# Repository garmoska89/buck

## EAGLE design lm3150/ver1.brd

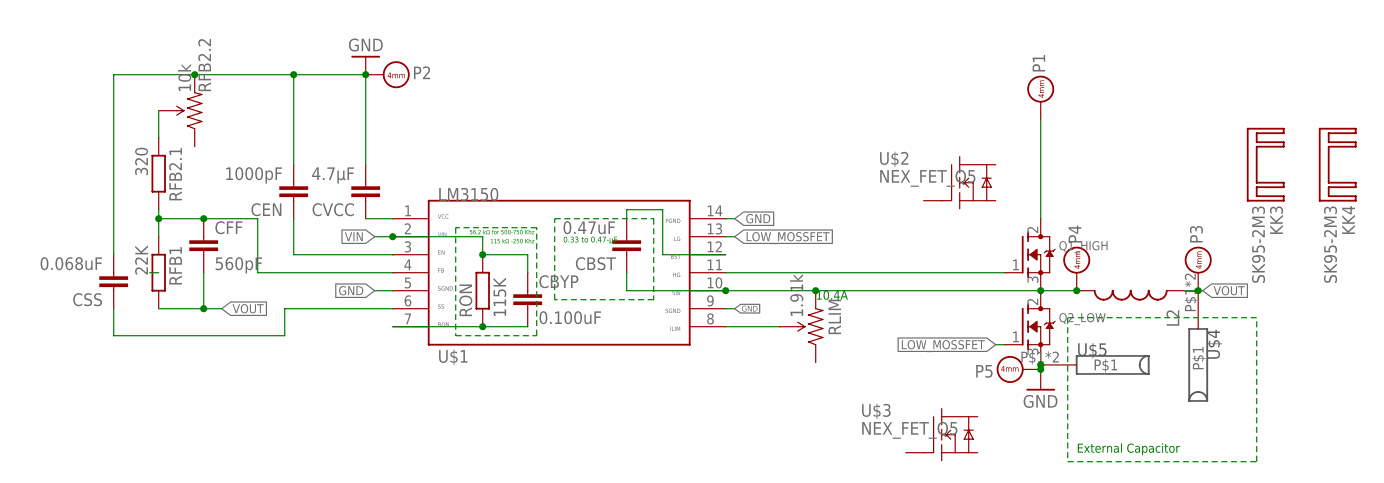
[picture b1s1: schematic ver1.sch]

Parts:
CBST: 0.47uF; 0805
CBYP: 0.100uF; 0805
CEN: 1000pF; 0805
CFF: 560pF; 0805
CSS: 0.068uF; 0805
CVCC: 4.7µF; 0805
KK3, KK4: SK95-2M3
L2: INDUCTOR; INDUCTOR-SRP4020
P1, P2, P3, P4, P5: BANANA
Q1_HIGH, Q2_LOW: MOSFET-NGDS_TO220V; TO220V
RFB1: 22K; R805
RFB2.1: 320; R805
RFB2.2: 10k; 3362U-2
RLIM: 1.91k; 3362U-2
RON: 115K; R805
U$1: LM3150; HTSSOP14
U$2, U$3: NEX_FET_Q5; Q5
U$4, U$5: BANANA

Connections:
GND: CEN.2, CSS.2, CVCC.2, P2.P$1, P5.P$1, Q2_LOW.3 (S), RFB2.2.3 (CW), U$1.5, U$1.9, U$1.14, U$5.P$1, U$5.P$2
HIGH_MOSSFET: Q1_HIGH.1 (G), U$1.11
LOW_MOSSFET: Q2_LOW.1 (G), U$1.13
unnamed: CVCC.1, U$1.1
unnamed: CBYP.2, RON.1, U$1.7
unnamed: CEN.1, U$1.3
unnamed: CSS.1, U$1.6
unnamed: CFF.1, RFB1.1, RFB2.1.2, U$1.4
unnamed: RFB2.1.1, RFB2.2.2 (WIPER)
unnamed: CBST.2, U$1.12
unnamed: RLIM.2 (WIPER), U$1.8
unnamed: CBST.1, L2.P$2 (2), P4.P$1, Q1_HIGH.3 (S), Q2_LOW.2 (D), RLIM.3 (CW), U$1.10
VIN: CBYP.1, P1.P$1, Q1_HIGH.2 (D), RON.2, U$1.2
VOUT: CFF.2, L2.P$1 (1), P3.P$1, RFB1.2

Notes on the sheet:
115 kΩ -250 Khz
56,2 kΩ for 500-750 Khz
0.33 to 0.47-µF
10.4A
External Capacitor

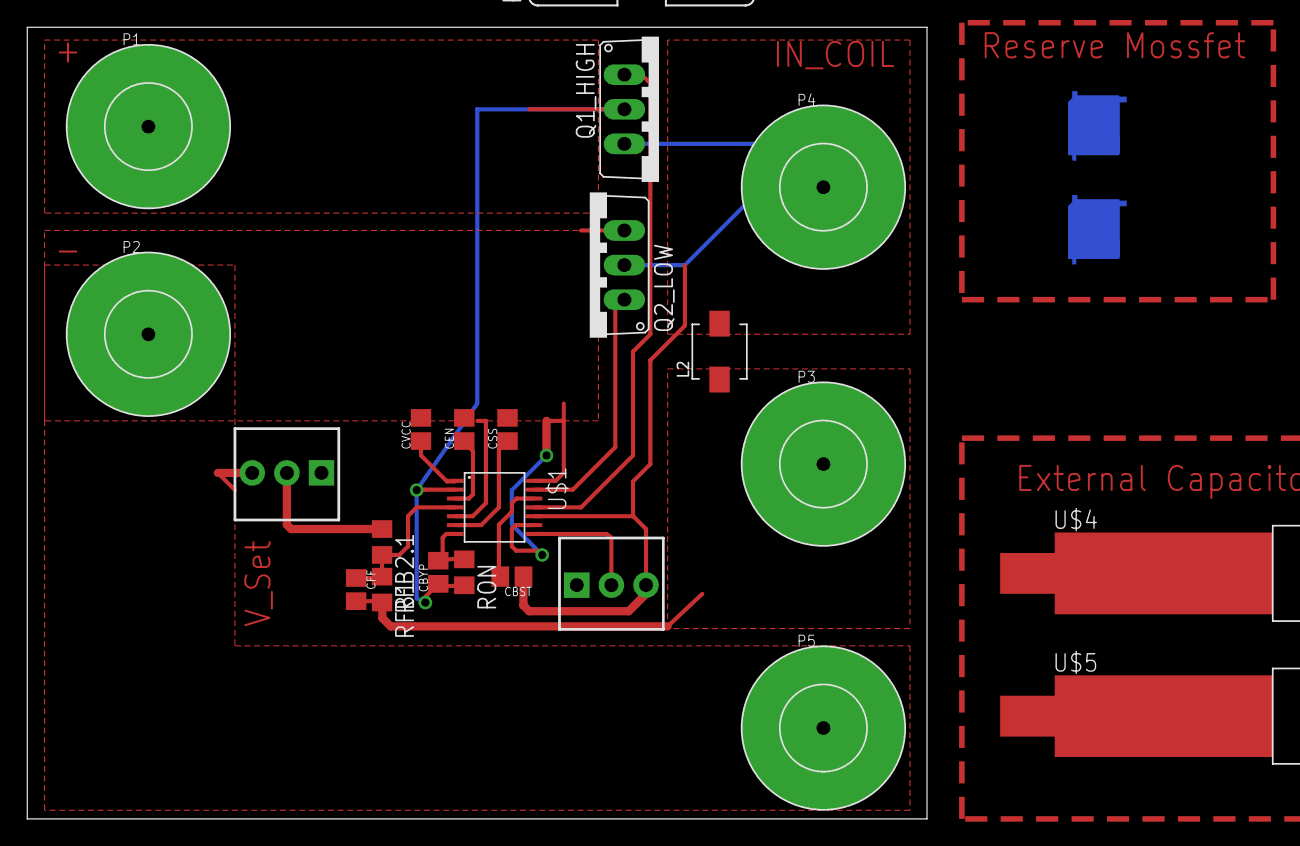
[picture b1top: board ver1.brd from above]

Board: 2 copper layers, 66.0 x 58.1 mm, 26 parts (0 on the bottom side), 14 nets.

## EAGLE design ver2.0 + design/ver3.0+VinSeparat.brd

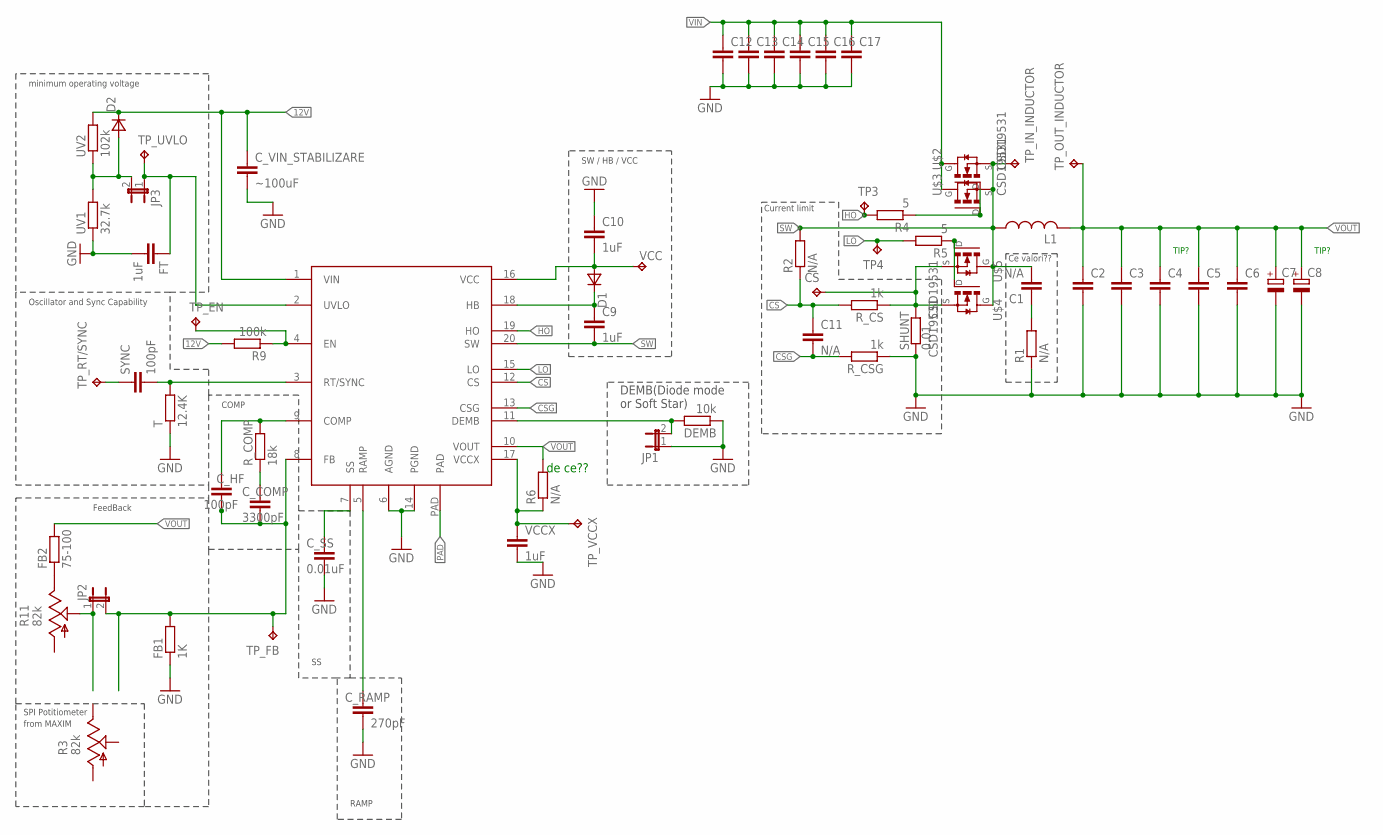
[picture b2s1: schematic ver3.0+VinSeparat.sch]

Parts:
C1, C11: N/A; C0805K
C2, C3, C4, C5, C6: C-EUC1812; C1812
C7, C8: CPOL-EU153CLV-1012; 153CLV-1012
C9, C10: 1uF; C0805K
C12, C13, C14, C15, C16, C17: C-EUC1812K; C1812K
CS: TPPAD1-20; P1-20
C_COMP: 3300pF; C0805K
C_HF: 100pF; C0805K
C_RAMP: 270pF; C0805K
C_SS: 0.01uF; C0805K
C_VIN_STABILIZARE: ~100uF; C0805K
D1, D2: DSOT23; SOT-23
DEMB: 10k; R0603
FB1: 1K; R0603
FB2: 75-100; R0603
FT: 1uF; C1812K
JP1, JP2, JP3: JP1E; JP1
L1: L-USTJ8-U2; TJ8-U2
R1: N/A; M1206
R2, R6: N/A; R0603
R3, R11: 82k; B64Y
R4, R5: 5; M1206
R9: 100k; R0603
R_COMP: 18k; R0603
R_CS: 1k; R0603
R_CSG: 1k; R0603
SHUNT: 0.01; SMR-0
SYNC: 100pF; C0805K
T: 12.4K; R0603
TP3, TP4: TPPAD1-20; P1-20
TP_EN: TPPAD1-20; P1-20
TP_FB: TPPAD1-20; P1-20
TP_IN_INDUCTOR: TPPAD1-20; P1-20
TP_OUT_INDUCTOR: TPPAD1-20; P1-20
TP_RT/SYNC: TPPAD1-20; P1-20
TP_UVLO: TPPAD1-20; P1-20
TP_VCCX: TPPAD1-20; P1-20
U$1: LM5116; TSSOP20
U$2, U$3, U$4, U$5: CSD19531; TO220H
UV1: 32.7k; R0603
UV2: 102k; R0603
VCC: TPPAD1-20; P1-20
VCCX: 1uF; C0805K

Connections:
12V: C_VIN_STABILIZARE.1, D2.1 (C), R9.2, U$1.1 (VIN), UV2.2
CS: C11.1, R2.1, R_CS.2, U$1.12 (CS)
CSG: C11.2, R_CSG.2, U$1.13 (CSG)
DEMB: DEMB.2, JP1.2, U$1.11 (DEMB)
GND: C2.2, C3.2, C4.2, C5.2, C6.2, C7.-, C8.-, C10.1, C12.2, C13.2, C14.2, C15.2, C16.2, C17.2, C_RAMP.2, C_SS.2, C_VIN_STABILIZARE.2, DEMB.1, FB1.1, FT.2, JP1.1, R1.1, R_CSG.1, SHUNT.2, T.1, U$1.6 (AGND), U$1.14 (PGND), UV1.1, VCCX.2
HB: C9.1, D1.1 (C), U$1.18 (HB)
HO: R4.2, TP3.TP, U$1.19 (HO)
LO: R5.2, TP4.TP, U$1.15 (LO)
unnamed: R6.1, TP_VCCX.TP, U$1.17 (VCCX), VCCX.1
unnamed: C1.1, R1.2
unnamed: CS.TP, R_CS.1, SHUNT.1, U$4.3 (S), U$5.3 (S)
unnamed: R9.1, TP_EN.TP, U$1.4 (EN)
unnamed: SYNC.2, T.2, U$1.3 (RT/SYNC)
unnamed: R4.1, U$2.1 (G), U$3.1 (G)
unnamed: SYNC.1, TP_RT/SYNC.TP
unnamed: FB2.1, R11.E
unnamed: C_HF.1, R_COMP.2, U$1.9 (COMP)
unnamed: C_COMP.1, R_COMP.1
unnamed: C_SS.1, U$1.7 (SS)
unnamed: C_RAMP.1, U$1.5 (RAMP)
unnamed: JP2.1, R11.S
unnamed: FT.1, JP3.1, TP_UVLO.TP, U$1.2 (UVLO)
unnamed: C_COMP.2, C_HF.2, FB1.2, JP2.2, TP_FB.TP, U$1.8 (FB)
unnamed: R5.1, U$4.1 (G), U$5.1 (G)
PAD: U$1.PAD
SW: C1.2, C9.2, L1.1, R2.2, TP_IN_INDUCTOR.TP, U$1.20 (SW), U$2.3 (S), U$3.3 (S), U$4.2 (D), U$4.T (D), U$5.2 (D), U$5.T (D)
UVLO: D2.3 (A), JP3.2, UV1.2, UV2.1
VCC: C10.2, D1.3 (A), U$1.16 (VCC), VCC.TP
VIN: C12.1, C13.1, C14.1, C15.1, C16.1, C17.1, U$2.2 (D), U$2.T (D), U$3.2 (D), U$3.T (D)
VOUT: C2.1, C3.1, C4.1, C5.1, C6.1, C7.+, C8.+, FB2.2, L1.2, R6.2, TP_OUT_INDUCTOR.TP, U$1.10 (VOUT)

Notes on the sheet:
TIP?
minimum operating voltage
Oscillator and Sync Capability
COMP
FeedBack
RAMP
DEMB(Diode mode or Soft Star)
SW / HB / VCC
Current limit
SPI Potitiometer
from MAXIM
Ce valori??
de ce??

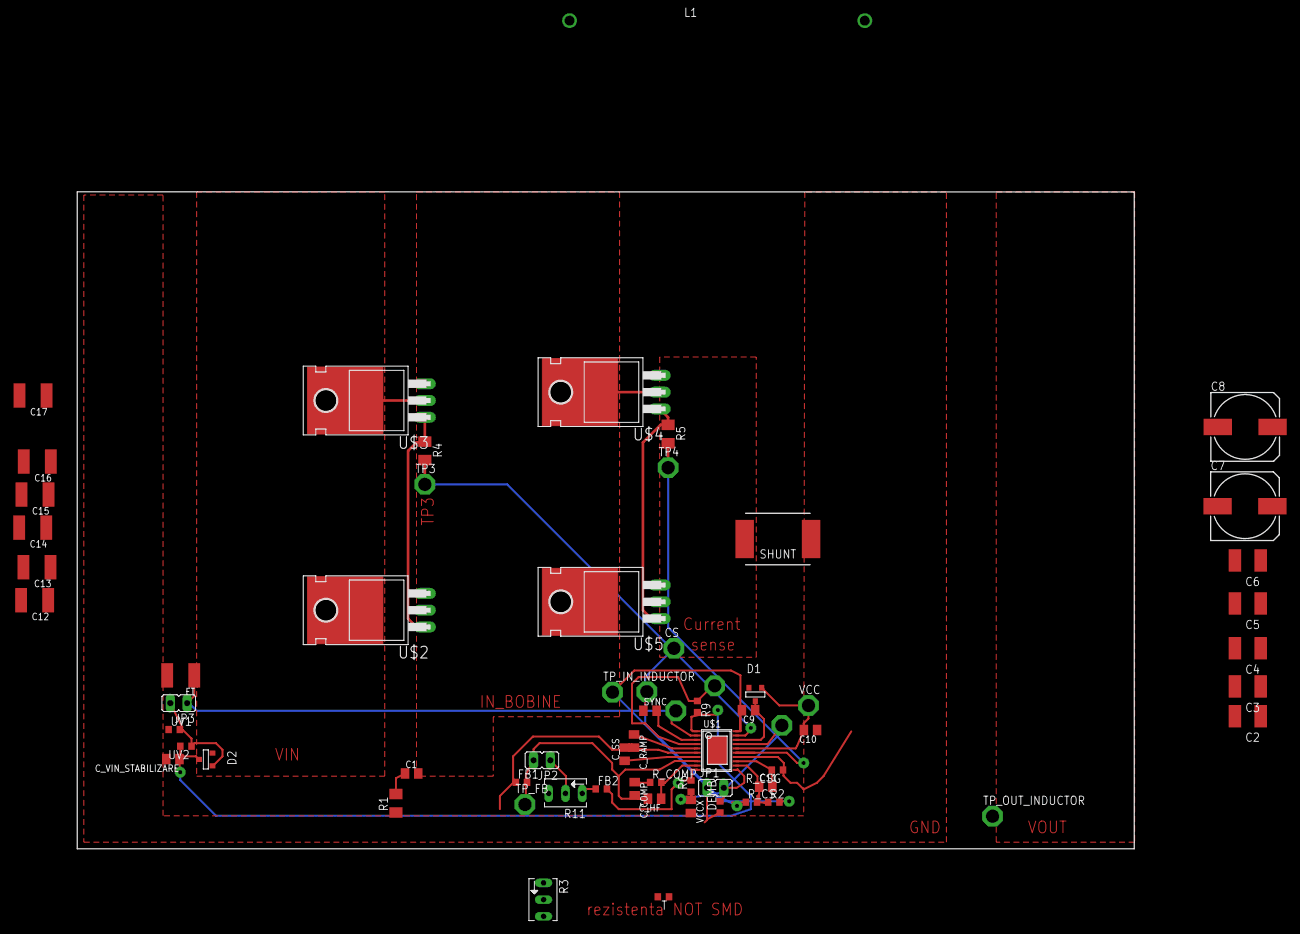
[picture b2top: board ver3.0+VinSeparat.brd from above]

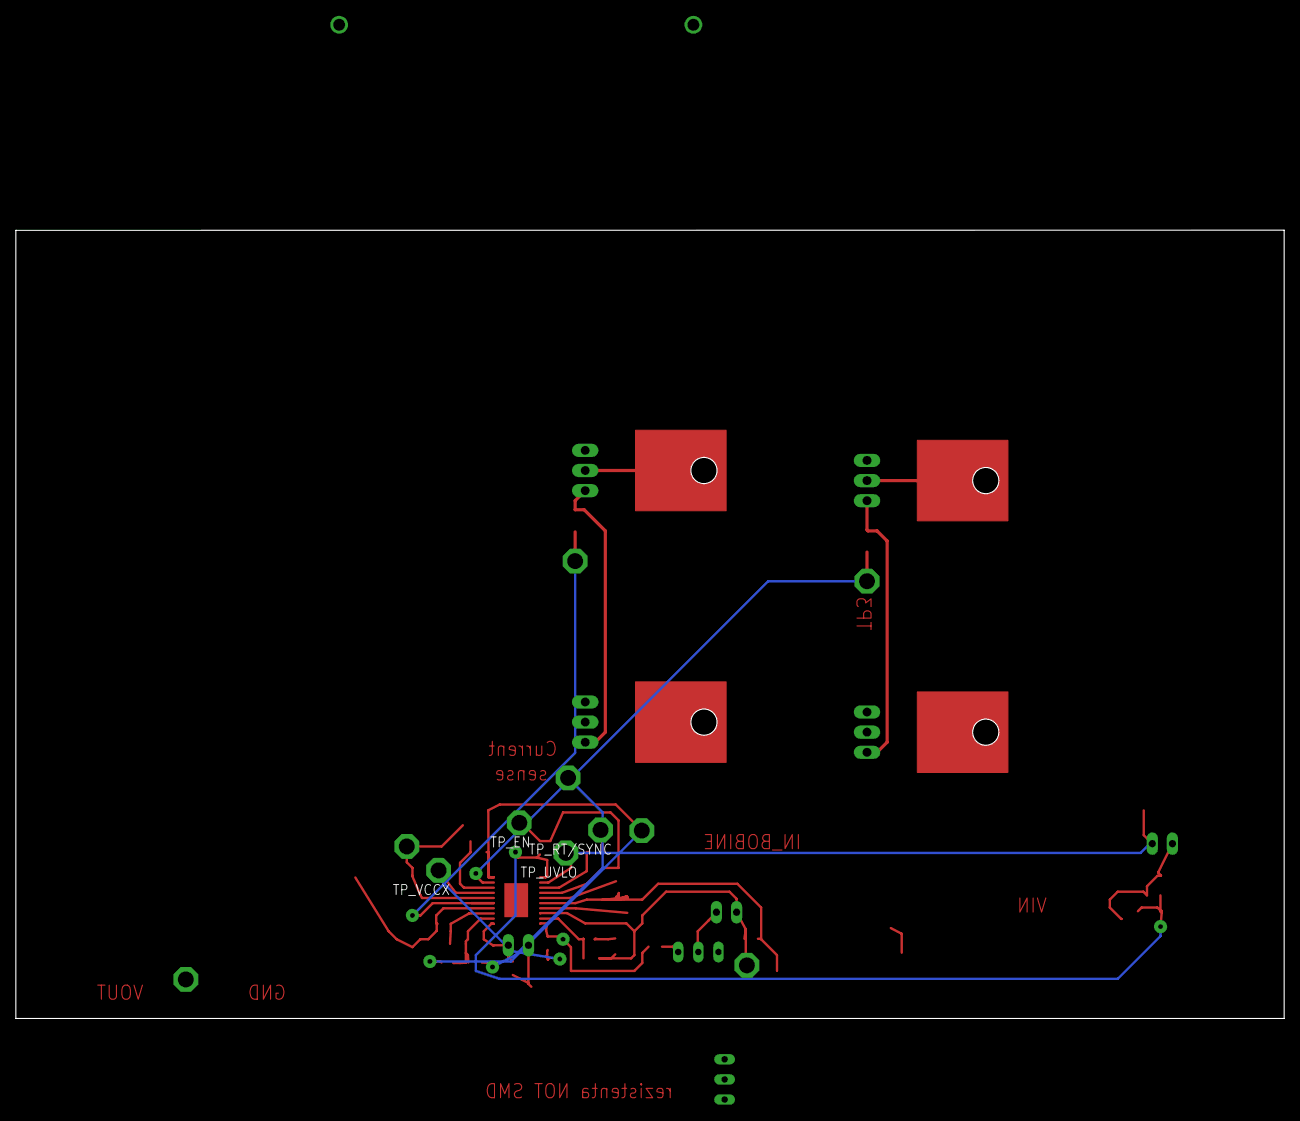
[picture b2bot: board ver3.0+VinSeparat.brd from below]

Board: 2 copper layers, 160.1 x 99.5 mm, 65 parts (4 on the bottom side), 29 nets.

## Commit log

2015-04-27 First modeling in Eagle
2015-04-28 version 2.0
2015-04-28 update excel file
2015-05-06 corectare trasee
2016-02-22 lm3150 buck first version
2018-04-04 04.04.2018

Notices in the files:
parts and their libraries:
SparkFun-Electromechanical: Licensing: Creative Commons ShareAlike 4.0 International - https://creativecommons.org/licenses/by-sa/4.0
